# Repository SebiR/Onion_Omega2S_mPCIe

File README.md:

# Onion Omega2S+ as mini PCIe card

WORK IN PROGRESS

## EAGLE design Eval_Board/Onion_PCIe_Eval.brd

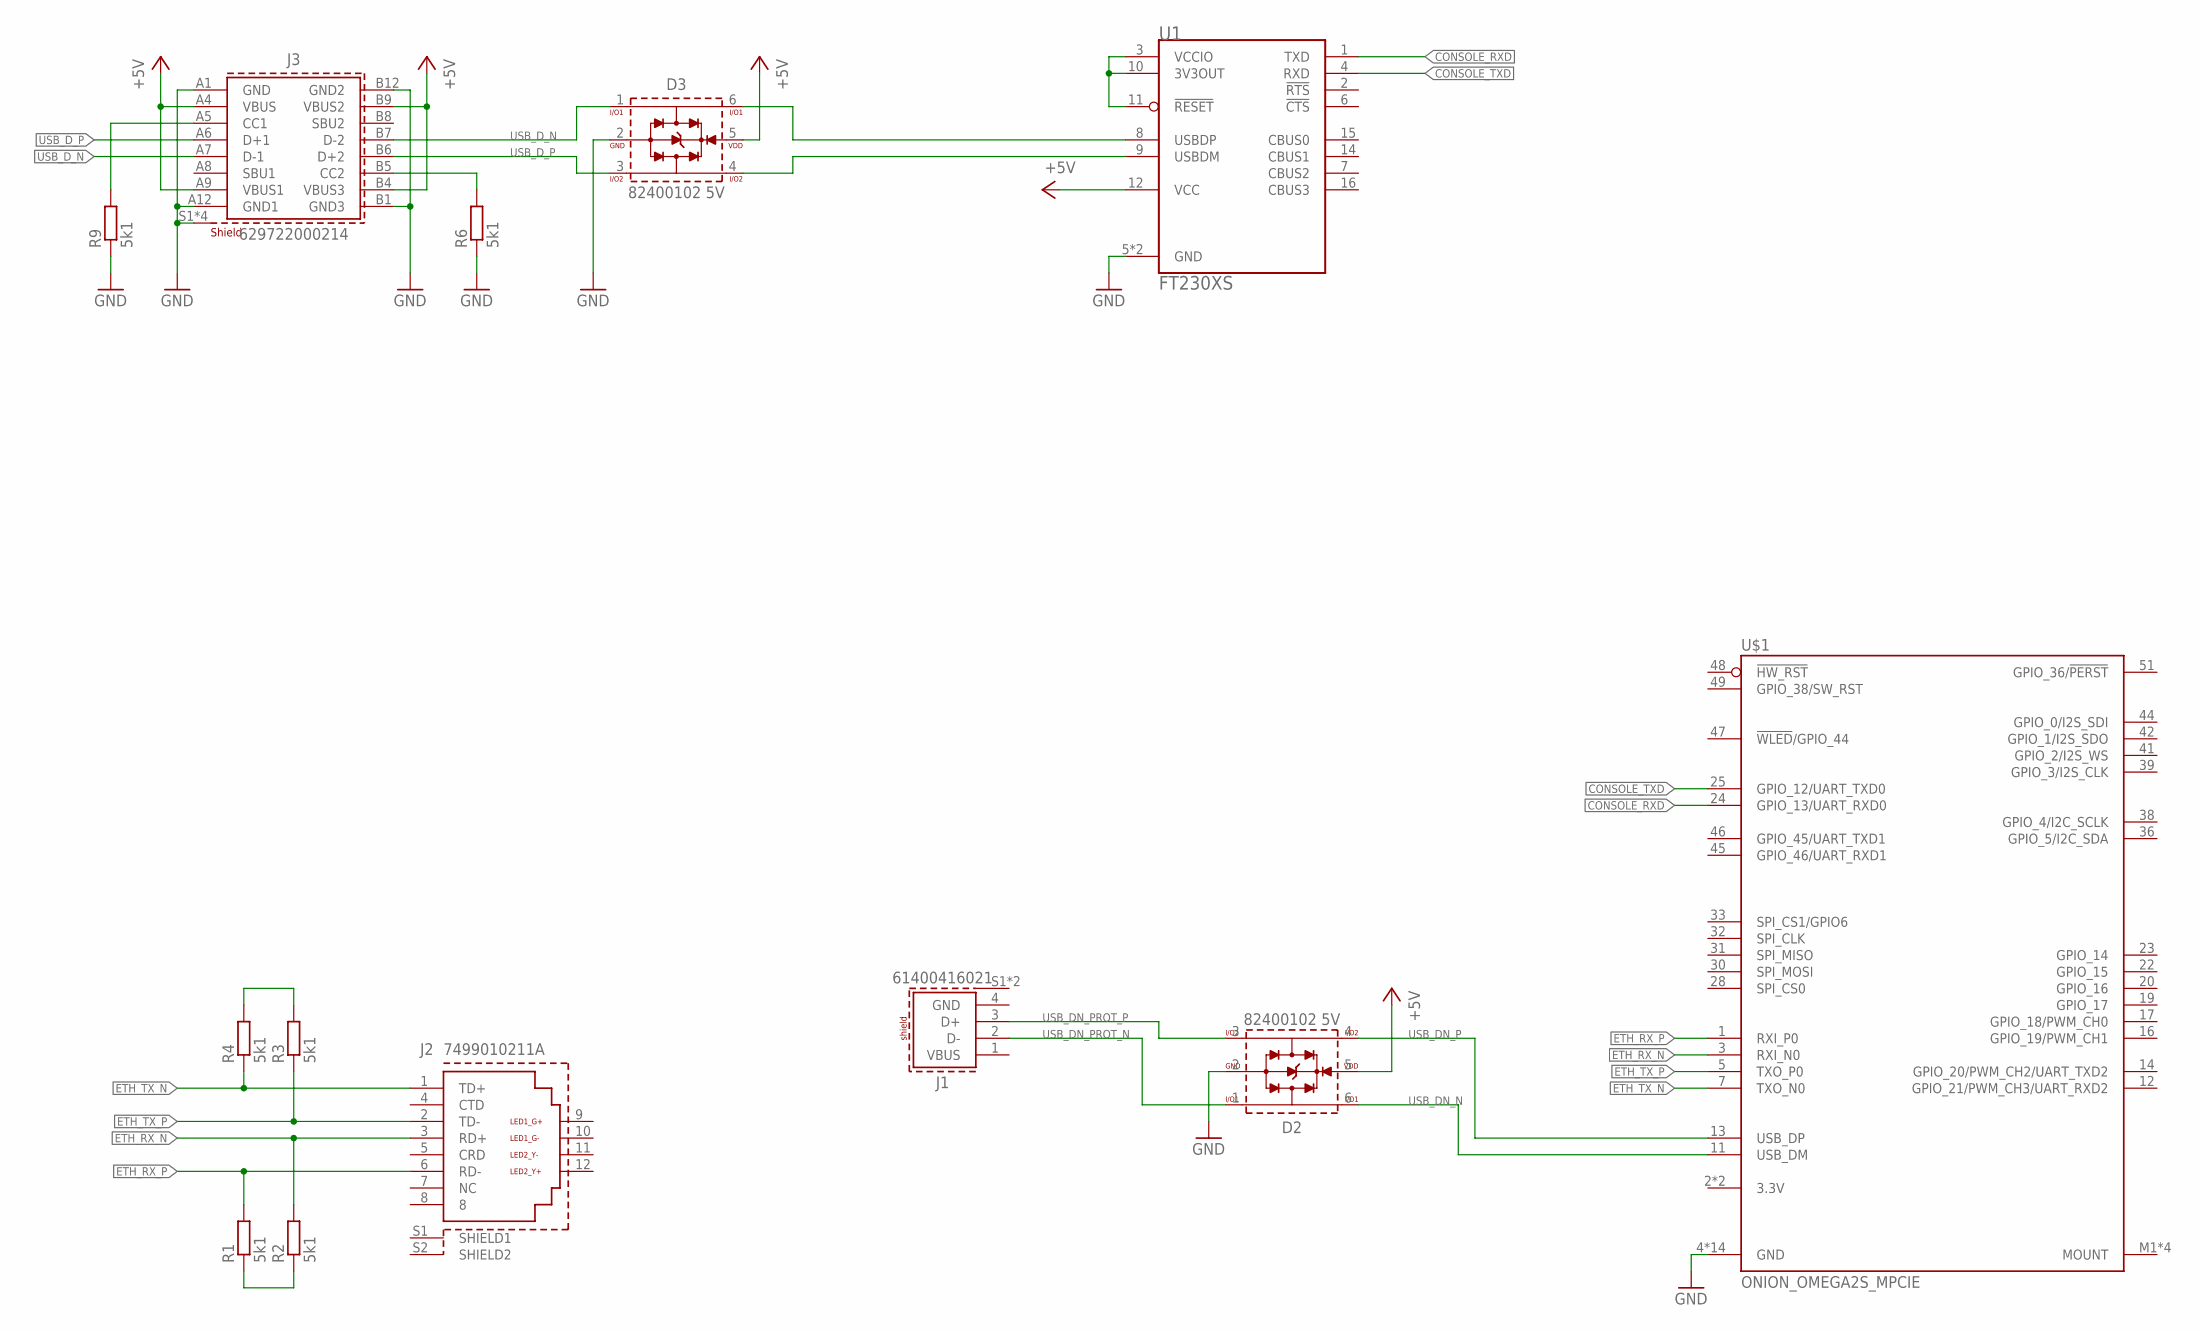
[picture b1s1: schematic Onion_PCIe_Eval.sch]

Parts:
D2, D3: 82400102 5V; WE-TVS_SOT23-6L
J1: 61400416021
J2: 7499010211A
J3: 629722000214
R1, R2, R3, R4, R6, R9: 5k1; R0603
U1: FT230XS; SSOP-16_FTD
U$1: ONION_OMEGA2S_MPCIE; MINI_PCIE_CONNECTOR_5.2H

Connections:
+5V: D2.5 (VDD), D3.5 (VDD), J3.A4 (VBUS), J3.A9 (VBUS1), J3.B4 (VBUS3), J3.B9 (VBUS2), U1.12 (VCC)
CONSOLE_RXD: U1.1 (TXD), U$1.24 (GPIO_13/UART_RXD0)
CONSOLE_TXD: U1.4 (RXD), U$1.25 (GPIO_12/UART_TXD0)
ETH_RX_N: J2.3 (RD+), R2.2, U$1.3 (RXI_N0)
ETH_RX_P: J2.6 (RD-), R1.2, U$1.1 (RXI_P0)
ETH_TX_N: J2.1 (TD+), R4.1, U$1.7 (TXO_N0)
ETH_TX_P: J2.2 (TD-), R3.1, U$1.5 (TXO_P0)
GND: D2.2 (GND), D3.2 (GND), J3.A1 (GND), J3.A12 (GND1), J3.B1 (GND3), J3.B12 (GND2), J3.S1 (SHIELD), J3.S2 (SHIELD), J3.S3 (SHIELD), J3.S4 (SHIELD), R6.1, R9.1, U1.5 (GND), U1.13 (GND), U$1.4 (GND), U$1.9 (GND), U$1.15 (GND), U$1.18 (GND), U$1.21 (GND), U$1.26 (GND), U$1.27 (GND), U$1.29 (GND), U$1.34 (GND), U$1.35 (GND), U$1.37 (GND), U$1.40 (GND), U$1.43 (GND), U$1.50 (GND)
unnamed: R1.1, R2.1
unnamed: J3.A5 (CC1), R9.2
unnamed: R3.2, R4.2
unnamed: U1.3 (VCCIO), U1.10 (3V3OUT), U1.11 (!RESET)
unnamed: J3.B5 (CC2), R6.2
USB_DN_N: D2.6 (I/O3), U$1.11 (USB_DM)
USB_DN_P: D2.4 (I/O4), U$1.13 (USB_DP)
USB_DN_PROT_N: D2.1 (I/O1), J1.2 (D-)
USB_DN_PROT_P: D2.3 (I/O2), J1.3 (D+)
USB_D_N: D3.1 (I/O1), J3.A7 (D-1), J3.B7 (D-2)
USB_D_P: D3.3 (I/O2), J3.A6 (D+1), J3.B6 (D+2)
USB_D_PROT_N: D3.6 (I/O3), U1.8 (USBDP)
USB_D_PROT_P: D3.4 (I/O4), U1.9 (USBDM)

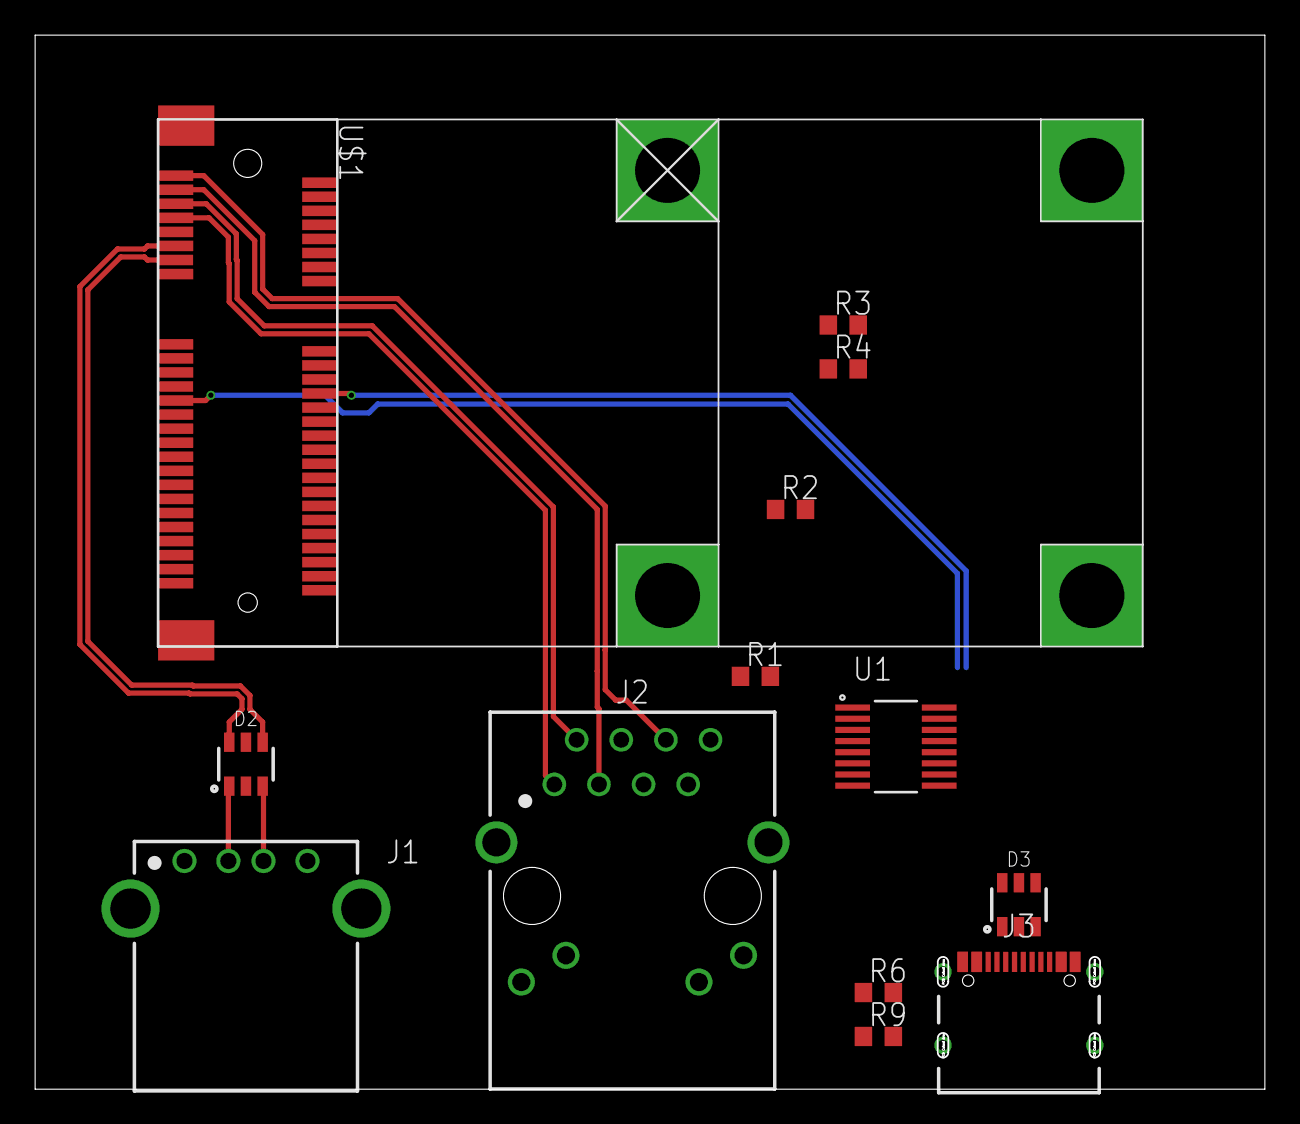
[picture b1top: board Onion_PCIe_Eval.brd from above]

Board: 4 copper layers, 69.9 x 59.9 mm, 13 parts (0 on the bottom side), 21 nets.

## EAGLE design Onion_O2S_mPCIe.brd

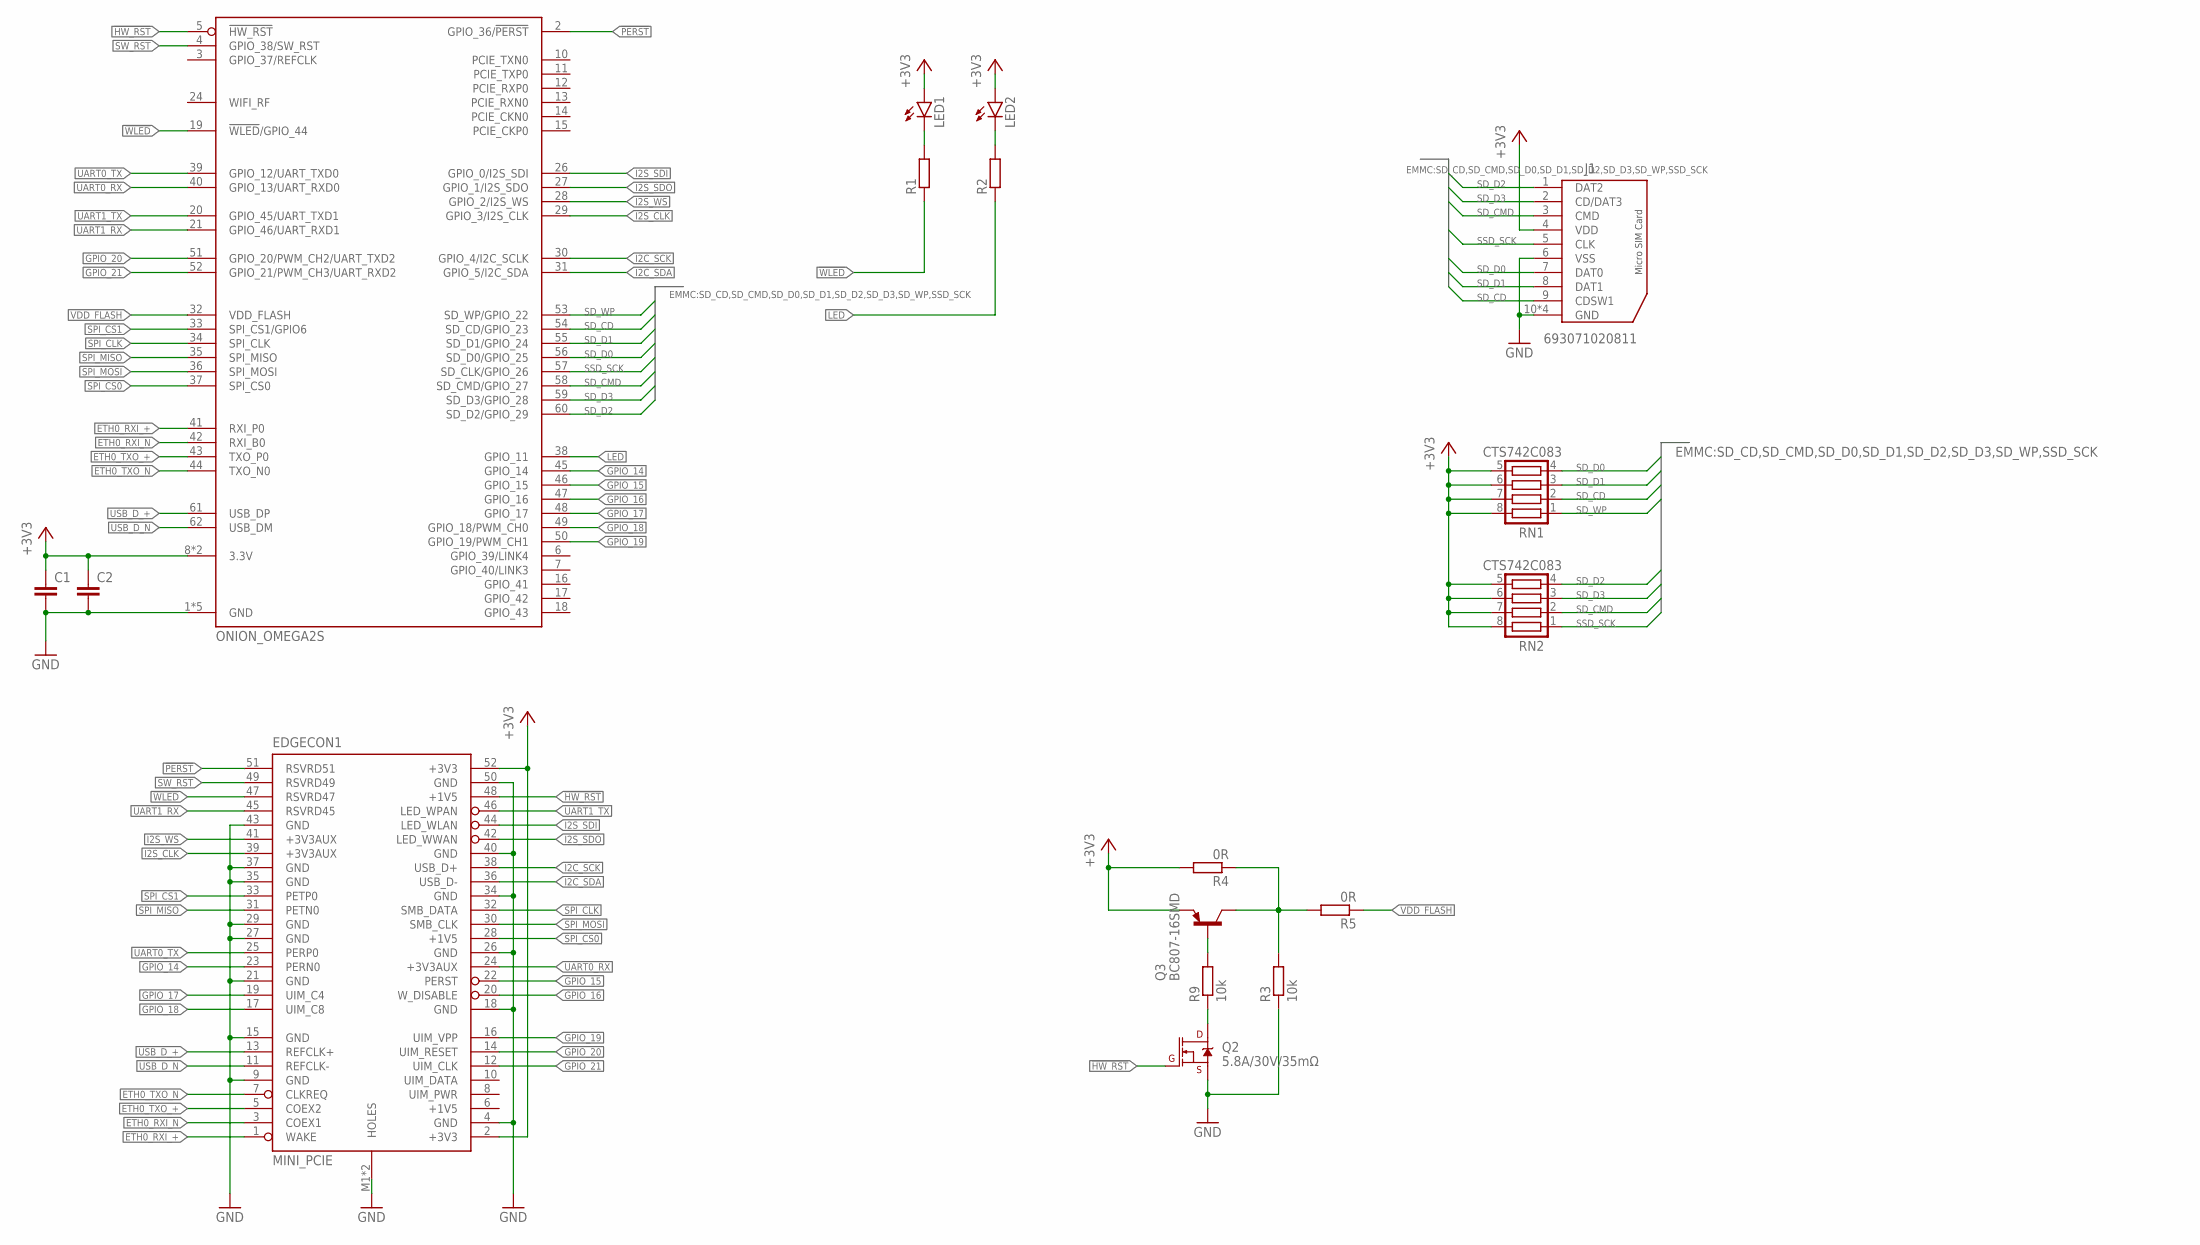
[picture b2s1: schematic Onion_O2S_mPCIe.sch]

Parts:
C1, C2: C-EUC0603; C0603
EDGECON1: MINI_PCIE
J1: 693071020811
LED1, LED2: LEDCHIPLED_0603; CHIPLED_0603
Q2: 5.8A/30V/35mΩ; SOT23-3
Q3: BC807-16SMD; SOT23-BEC
R1, R2: R-EU_R0603; R0603
R3, R9: 10k; R0603
R4, R5: 0R; R0603
RN1, RN2: CTS742C083
U1: ONION_OMEGA2S

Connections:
!HW_RST: EDGECON1.48 (+1V5), Q2.1 (G), U1.5 (!HW_RST)
!PERST: EDGECON1.51 (RSVRD51), U1.2 (GPIO_36/!PERST)
!WLED: EDGECON1.47 (RSVRD47), R1.1, U1.19 (!WLED!/GPIO_44)
+1V5: EDGECON1.6 (+1V5)
+3V3: C1.1, C2.1, EDGECON1.2 (+3V3), EDGECON1.52 (+3V3), J1.4 (VDD), LED1.A, LED2.A, Q3.E, R4.2, RN1.5, RN1.6, RN1.7, RN1.8, RN2.5, RN2.6, RN2.7, RN2.8, U1.8 (3.3V), U1.9 (3.3V)
ETH0_RXI_+: EDGECON1.1 (WAKE), U1.41 (RXI_P0)
ETH0_RXI_N: EDGECON1.3 (COEX1), U1.42 (RXI_B0)
ETH0_TXO_+: EDGECON1.5 (COEX2), U1.43 (TXO_P0)
ETH0_TXO_N: EDGECON1.7 (CLKREQ), U1.44 (TXO_N0)
GND: C1.2, C2.2, EDGECON1.4 (GND), EDGECON1.9 (GND), EDGECON1.15 (GND), EDGECON1.18 (GND), EDGECON1.21 (GND), EDGECON1.26 (GND), EDGECON1.27 (GND), EDGECON1.29 (GND), EDGECON1.34 (GND), EDGECON1.35 (GND), EDGECON1.37 (GND), EDGECON1.40 (GND), EDGECON1.43 (GND), EDGECON1.50 (GND), EDGECON1.M1 (HOLES), EDGECON1.M2 (HOLES), J1.6 (VSS), J1.10 (GND), J1.11 (GND), J1.12 (GND), J1.13 (GND), Q2.2 (S), R3.1, U1.1 (GND), U1.22 (GND), U1.23 (GND), U1.25 (GND), U1.63 (GND)
GPIO_14: EDGECON1.23 (PERN0), U1.45 (GPIO_14)
GPIO_15: EDGECON1.22 (PERST), U1.46 (GPIO_15)
GPIO_16: EDGECON1.20 (W_DISABLE), U1.47 (GPIO_16)
GPIO_17: EDGECON1.19 (UIM_C4), U1.48 (GPIO_17)
GPIO_18: EDGECON1.17 (UIM_C8), U1.49 (GPIO_18/PWM_CH0)
GPIO_19: EDGECON1.16 (UIM_VPP), U1.50 (GPIO_19/PWM_CH1)
GPIO_20: EDGECON1.14 (UIM_RESET), U1.51 (GPIO_20/PWM_CH2/UART_TXD2)
GPIO_21: EDGECON1.12 (UIM_CLK), U1.52 (GPIO_21/PWM_CH3/UART_RXD2)
I2C_SCK: EDGECON1.38 (USB_D+), U1.30 (GPIO_4/I2C_SCLK)
I2C_SDA: EDGECON1.36 (USB_D-), U1.31 (GPIO_5/I2C_SDA)
I2S_CLK: EDGECON1.39 (+3V3AUX), U1.29 (GPIO_3/I2S_CLK)
I2S_SDI: EDGECON1.44 (LED_WLAN), U1.26 (GPIO_0/I2S_SDI)
I2S_SDO: EDGECON1.42 (LED_WWAN), U1.27 (GPIO_1/I2S_SDO)
I2S_WS: EDGECON1.41 (+3V3AUX), U1.28 (GPIO_2/I2S_WS)
LED: R2.1, U1.38 (GPIO_11)
unnamed: LED1.C, R1.2
unnamed: Q3.B, R9.2
unnamed: Q2.3 (D), R9.1
unnamed: Q3.C, R3.2, R4.1, R5.2
unnamed: LED2.C, R2.2
SD_CD: J1.9 (CDSW1), RN1.2, U1.54 (SD_CD/GPIO_23)
SD_CMD: J1.3 (CMD), RN2.2, U1.58 (SD_CMD/GPIO_27)
SD_D0: J1.7 (DAT0), RN1.4, U1.56 (SD_D0/GPIO_25)
SD_D1: J1.8 (DAT1), RN1.3, U1.55 (SD_D1/GPIO_24)
SD_D2: J1.1 (DAT2), RN2.4, U1.60 (SD_D2/GPIO_29)
SD_D3: J1.2 (CD/DAT3), RN2.3, U1.59 (SD_D3/GPIO_28)
SD_WP: RN1.1, U1.53 (SD_WP/GPIO_22)
SPI_CLK: EDGECON1.32 (SMB_DATA), U1.34 (SPI_CLK)
SPI_CS0: EDGECON1.28 (+1V5), U1.37 (SPI_CS0)
SPI_CS1: EDGECON1.33 (PETP0), U1.33 (SPI_CS1/GPIO6)
SPI_MISO: EDGECON1.31 (PETN0), U1.35 (SPI_MISO)
SPI_MOSI: EDGECON1.30 (SMB_CLK), U1.36 (SPI_MOSI)
SSD_SCK: J1.5 (CLK), RN2.1, U1.57 (SD_CLK/GPIO_26)
SW_RST: EDGECON1.49 (RSVRD49), U1.4 (GPIO_38/SW_RST)
UART0_RX: EDGECON1.24 (+3V3AUX), U1.40 (GPIO_13/UART_RXD0)
UART0_TX: EDGECON1.25 (PERP0), U1.39 (GPIO_12/UART_TXD0)
UART1_RX: EDGECON1.45 (RSVRD45), U1.21 (GPIO_46/UART_RXD1)
UART1_TX: EDGECON1.46 (LED_WPAN), U1.20 (GPIO_45/UART_TXD1)
USB_D_+: EDGECON1.13 (REFCLK+), U1.61 (USB_DP)
USB_D_N: EDGECON1.11 (REFCLK-), U1.62 (USB_DM)
VDD_FLASH: R5.1, U1.32 (VDD_FLASH)

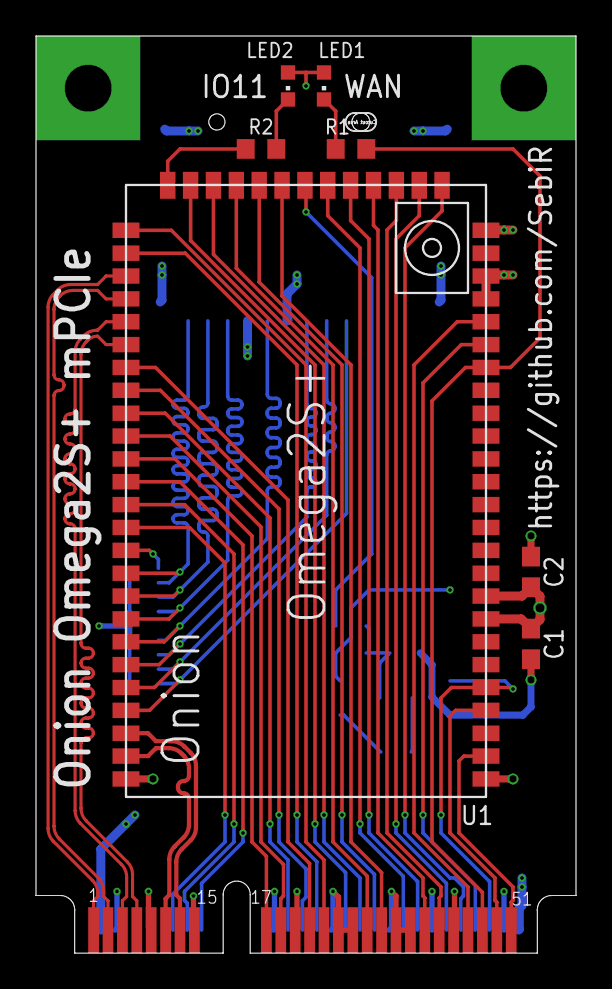
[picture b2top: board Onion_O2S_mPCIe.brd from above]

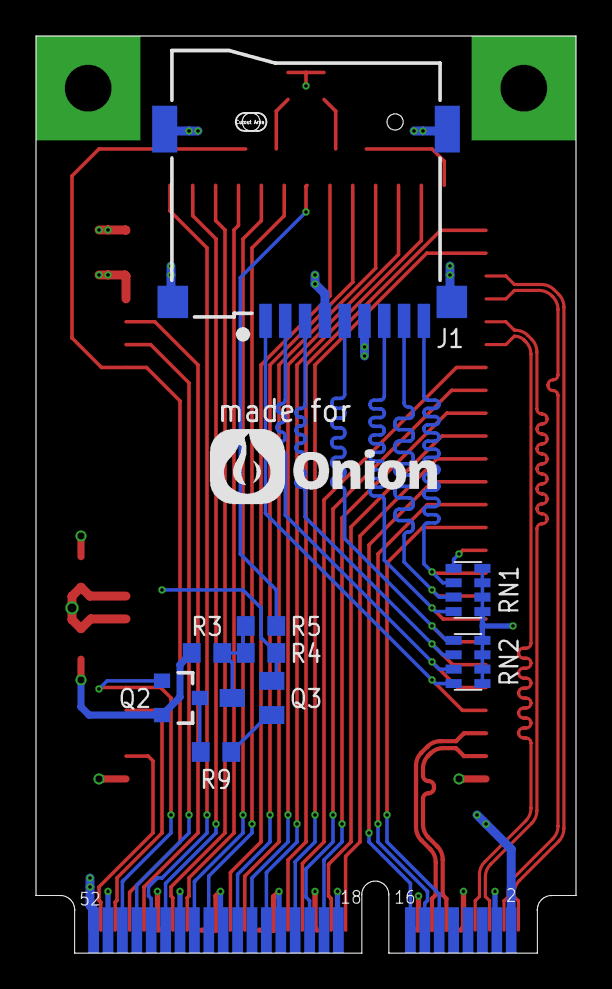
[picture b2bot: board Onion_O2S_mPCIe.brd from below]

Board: 4 copper layers, 29.9 x 50.9 mm, 17 parts (9 on the bottom side), 50 nets.

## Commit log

2024-08-10 continued layout
2024-08-25 * Completely changed pinout * Started Eval Board
2024-08-25 updated pictures
2024-08-29 - small changes to the sikscreen of the module - continued design of Eval Board

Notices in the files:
parts and their libraries:
Wurth_EMC Components_WE-TVS: Copyright: Würth Elektronik
COPYRIGHT: Copyright (C) 2024 Ultra Librarian. All rights reserved.
SparkFun-DiscreteSemi: Licensing: Creative Commons ShareAlike 4.0 International - https://creativecommons.org/licenses/by-sa/4.0
